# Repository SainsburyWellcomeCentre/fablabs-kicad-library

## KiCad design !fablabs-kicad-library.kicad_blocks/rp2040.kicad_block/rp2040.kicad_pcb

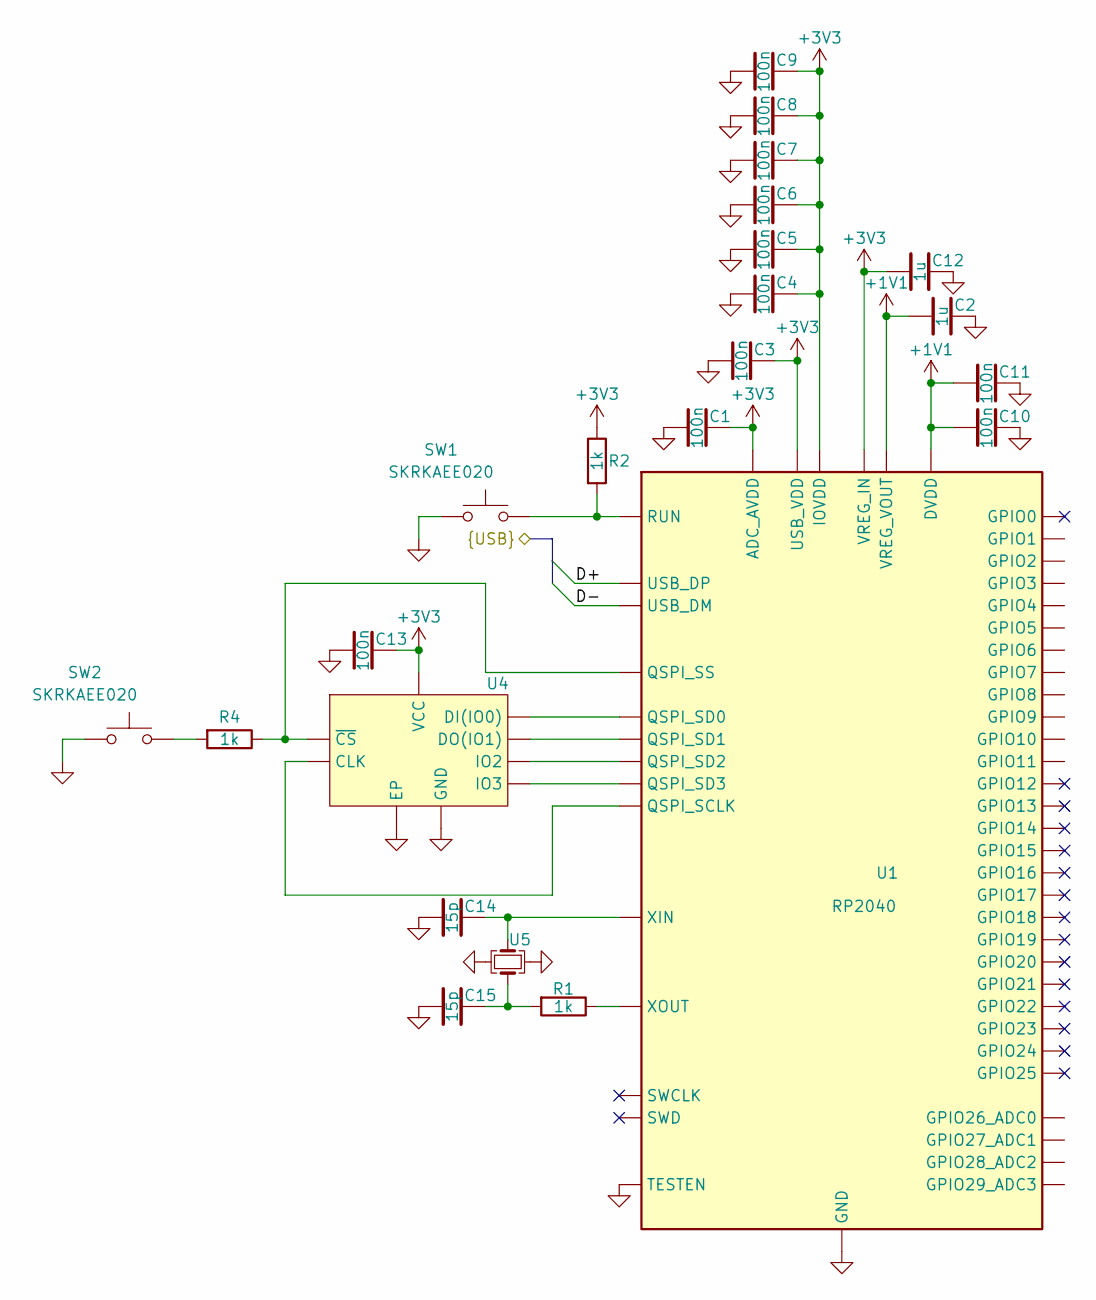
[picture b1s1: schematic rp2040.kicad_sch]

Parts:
C1, C3, C4, C5, C6, C7, C8, C9, C10, C11, C13: 100n; C_0402_1005M; MFR.Part # CL05B104KO5NNNC; JLCPCB Part # C1525
C2, C12: 1u; C_0402_1005M; MFR.Part # CL05A105KA5NQNC; JLCPCB Part # C52923
C14, C15: 15p; C_0402_1005M; Part Version 0.0.0; JLCPCB Part # C1548
R1, R2, R4: 1k; R_0402_1005M; Part Version 0.0.0; JLCPCB Part # C11702
SW1, SW2: SKRKAEE020; Part Version 0.0.0; LCSC Part C115357
U1: RP2040; QFN-56-1EP_7x7mm; Part Version 0.0.0; JLCPCB Part # C2040
U4: W25Q64JVXGIQ; XSON-8_L4.0-W4.0-P0.80-TL-EP; Part Version 0.0.0; JLCPCB Part # C2940195
U5: ABM8-272-T3_C20625731; XTAL-SMD_4P-L3.2-W2.5; Part Version 0.0.0; LCSC Part C20625731

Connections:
+1V1: C2.2, C10.1, C11.1, U1.23 (DVDD), U1.45 (VREG_VOUT), U1.50 (DVDD)
+3V3: C1.2, C3.2, C4.2, C5.2, C6.2, C7.2, C8.2, C9.2, C12.2, C13.2, R2.2, U1.1 (IOVDD), U1.10 (IOVDD), U1.22 (IOVDD), U1.33 (IOVDD), U1.42 (IOVDD), U1.43 (ADC_AVDD), U1.44 (VREG_IN), U1.48 (USB_VDD), U1.49 (IOVDD), U4.8 (VCC); also elsewhere on the board
/D+: U1.47 (USB_DP)
/D-: U1.46 (USB_DM)
GND: C1.1, C2.1, C3.1, C4.1, C5.1, C6.1, C7.1, C8.1, C9.1, C10.2, C11.2, C12.1, C13.1, C14.1, C15.2, SW1.1, SW2.1, U1.19 (TESTEN), U1.57 (GND), U4.4 (GND), U4.9 (EP), U5.2, U5.4
unnamed: C15.1, R1.1, U5.3
unnamed: R4.1, SW2.2
unnamed: U1.52 (QSPI_SCLK), U4.6 (CLK)
unnamed: U1.53 (QSPI_SD0), U4.5 (DI(IO0))
unnamed: U1.55 (QSPI_SD1), U4.2 (DO(IO1))
unnamed: U1.54 (QSPI_SD2), U4.3 (IO2)
unnamed: U1.51 (QSPI_SD3), U4.7 (IO3)
unnamed: R4.2, U1.56 (QSPI_SS), U4.1 (~CS)
unnamed 13: R2.1, SW1.2, U1.26 (RUN); also elsewhere on the board
unnamed: C14.2, U1.20 (XIN), U5.1
unnamed: R1.2, U1.21 (XOUT)

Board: 2 copper layers, 23 parts (0 on the bottom side), 14 nets, no tracks yet.

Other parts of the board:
R3: 1k; R_0402_1005M

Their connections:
+3V3: R3.2; also elsewhere on the board
unnamed 13: R3.1; also elsewhere on the board

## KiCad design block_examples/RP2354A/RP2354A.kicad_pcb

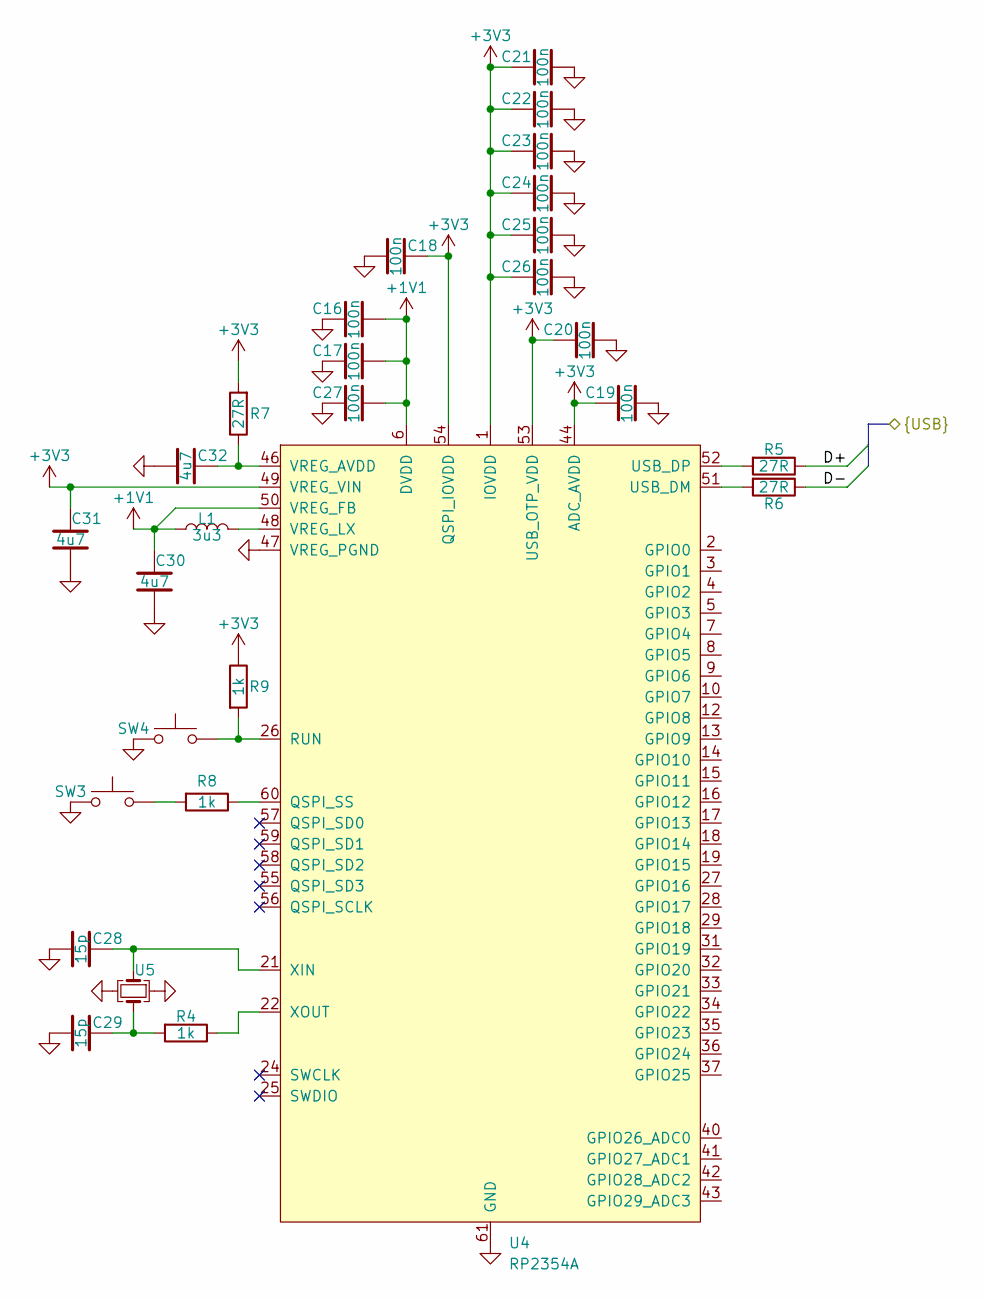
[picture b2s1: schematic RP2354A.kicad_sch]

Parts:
C16, C17, C18, C19, C20, C21, C22, C23, C24, C25, C26, C27: 100n; C_0402_1005M; MFR.Part # CL05B104KO5NNNC; JLCPCB Part # C1525
C28, C29: 15p; C_0402_1005M; Part Version 0.0.0; JLCPCB Part # C1548
C30, C31, C32: 4u7; C_0402_1005M; Part Version 0.0.0; JLCPCB Part # C2858031
L1: 3u3; IND_LQH2MPN3R3MGRL; Part Version 0.0.0; JLCPCB Part # C1329801
R4, R8, R9: 1k; R_0402_1005M; Part Version 0.0.0; JLCPCB Part # C11702
R5, R6, R7: 27R; R_0402_1005M; Part Version 0.0.0; JLCPCB Part # C25100
SW3, SW4: SKRKAEE020; Part Version 0.0.0; LCSC Part C115357
U4: RP2354A; QFN-60-1EP_7x7mm; Part Version 0.0.0; JLCPCB Part # C41378174
U5: ABM8-272-T3_C20625731; XTAL-SMD_4P-L3.2-W2.5; Part Version 0.0.0; LCSC Part C20625731

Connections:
+1V1: C16.1, C17.1, C27.1, C30.1, L1.2, U4.6 (DVDD), U4.23 (DVDD), U4.39 (DVDD), U4.50 (VREG_FB)
+3V3: C18.2, C19.2, C20.2, C21.2, C22.2, C23.2, C24.2, C25.2, C26.2, C31.1, R7.1, R9.2, U4.1 (IOVDD), U4.11 (IOVDD), U4.20 (IOVDD), U4.30 (IOVDD), U4.38 (IOVDD), U4.44 (ADC_AVDD), U4.45 (IOVDD), U4.49 (VREG_VIN), U4.53 (USB_OTP_VDD), U4.54 (QSPI_IOVDD)
/D+: R5.2
/D-: R6.2
GND: C16.2, C17.2, C18.1, C19.1, C20.1, C21.1, C22.1, C23.1, C24.1, C25.1, C26.1, C27.2, C28.1, C29.2, C30.2, C31.2, C32.2, SW3.1, SW4.1, U4.47 (VREG_PGND), U4.61 (GND), U5.2, U5.4
unnamed: C29.1, R4.1, U5.3
unnamed: R8.1, SW3.2
unnamed: R8.2, U4.60 (QSPI_SS)
unnamed: R9.1, SW4.2, U4.26 (RUN)
unnamed: R6.1, U4.51 (USB_DM)
unnamed: R5.1, U4.52 (USB_DP)
unnamed: C32.1, R7.2, U4.46 (VREG_AVDD)
unnamed: L1.1, U4.48 (VREG_LX)
unnamed: C28.2, U4.21 (XIN), U5.1
unnamed: R4.2, U4.22 (XOUT)

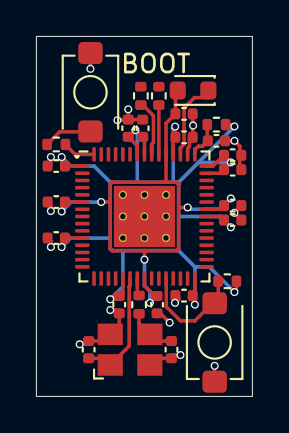
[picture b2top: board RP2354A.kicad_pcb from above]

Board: 4 copper layers, 12.0 x 20.0 mm, 28 parts (0 on the bottom side), 13 nets.
